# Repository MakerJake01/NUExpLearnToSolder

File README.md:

# ExpLearnToSolder
A simple learn to solder activity

## Parts
| Part      | Description |
| ----------- | ----------- |
| PCB   |  Black soldermask and white silkscreen |
| LED      | 5mm tht       |
| Battery   | 1225        |
| Battery holder  | Keystone 3000|
|Tie tack |    |
| Backing |    |

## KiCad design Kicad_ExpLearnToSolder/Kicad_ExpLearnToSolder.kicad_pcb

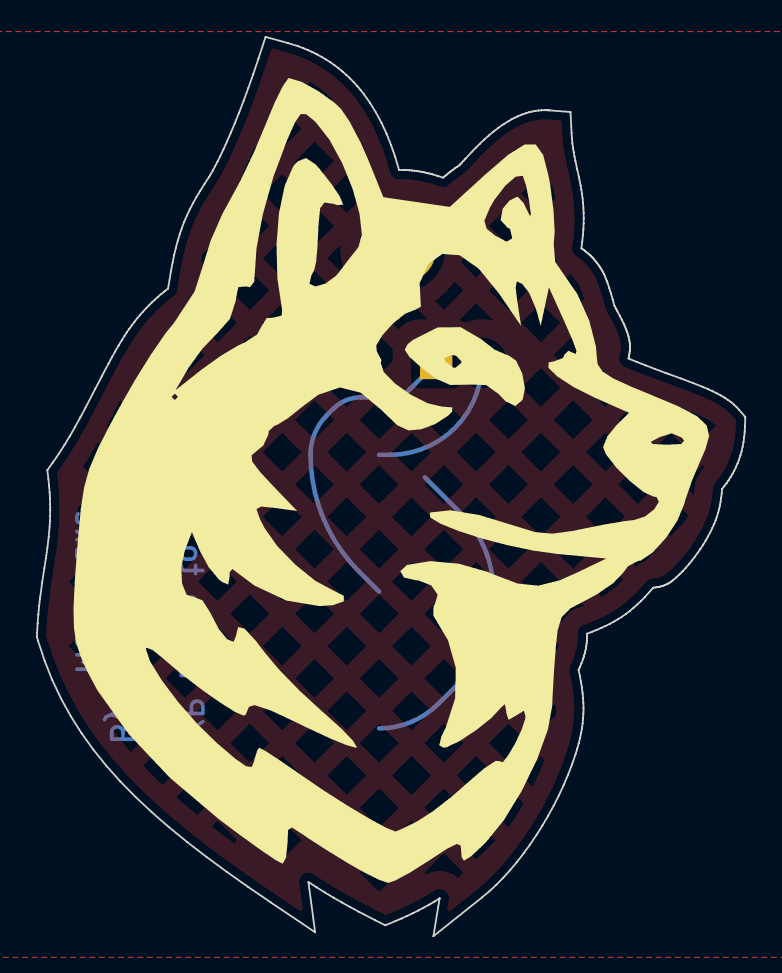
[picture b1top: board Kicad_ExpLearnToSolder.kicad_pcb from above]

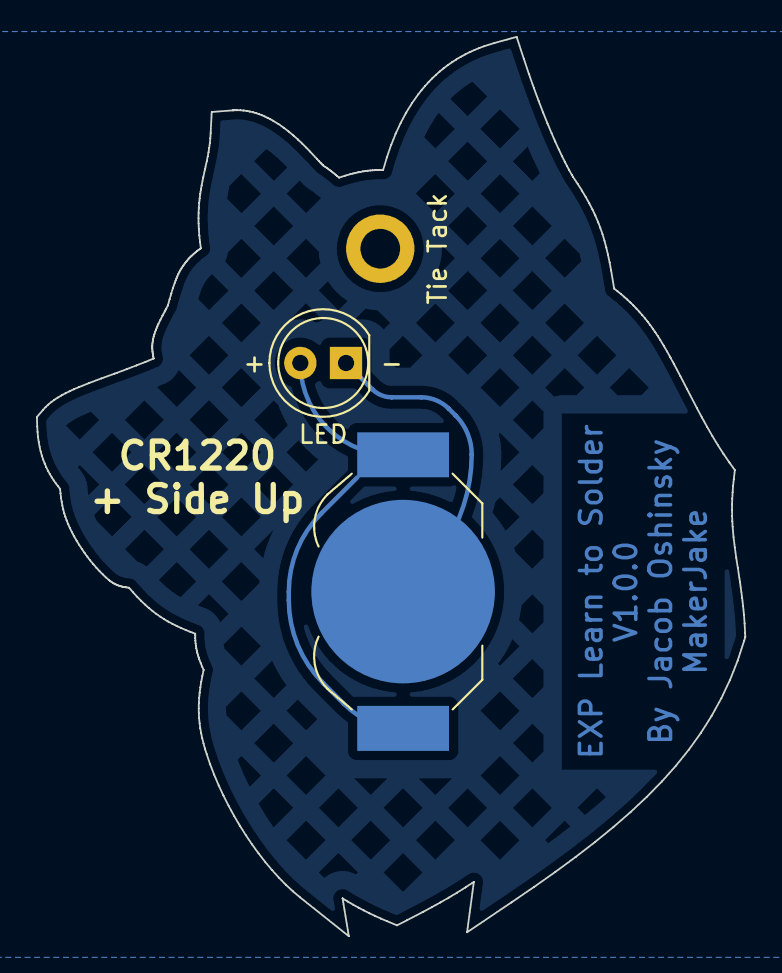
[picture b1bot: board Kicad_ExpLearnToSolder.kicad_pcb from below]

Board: 2 copper layers, 39.4 x 50.0 mm, 3 parts (2 on the bottom side), 2 nets.

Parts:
BT1: Battery_Cell; BatteryHolder_LINX_BAT-HLD-012-SMT
H1: Tie Tack; MountingHole_2.2mm_M2_DIN965_Pad
LED: LED; LED_D5.0mm

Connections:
GND: BT1.2 (-), LED.1 (K)
unnamed: BT1.1 (+), LED.2 (A)

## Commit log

2023-10-18 adding needed files and kicad
2023-10-18 flipped LED 3d preview and added backups to the gitignore
2023-10-18 removed un needed backups
